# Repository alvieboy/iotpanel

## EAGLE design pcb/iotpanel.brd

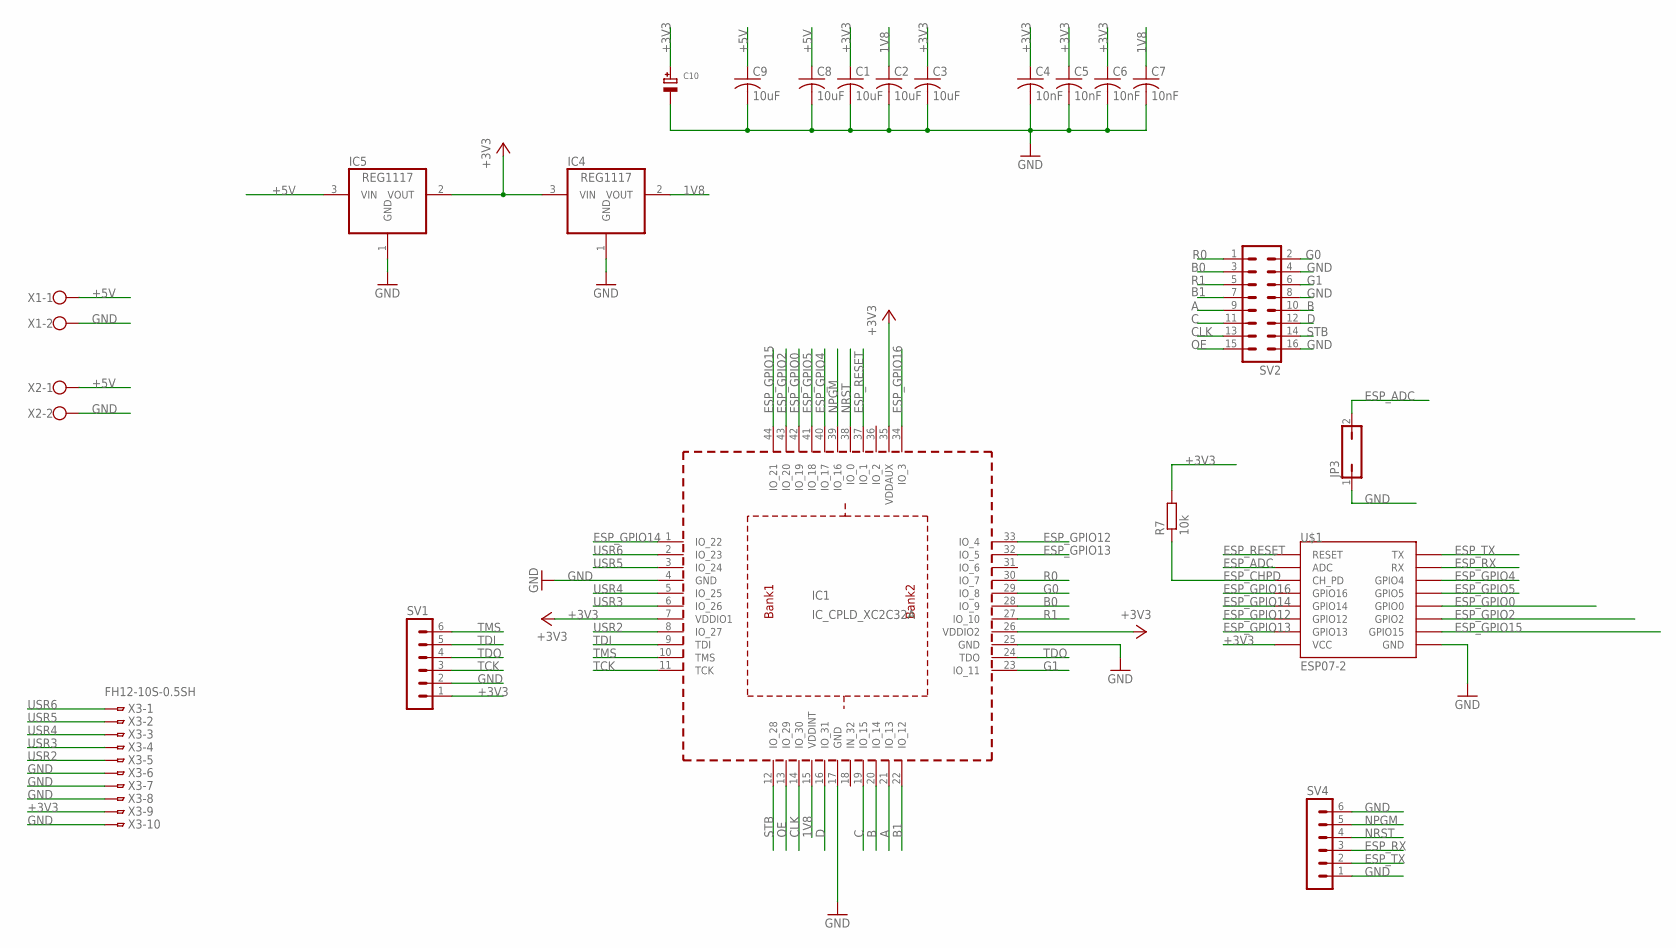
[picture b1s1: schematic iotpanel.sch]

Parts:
C1, C2, C3, C8, C9: 10uF; CAPC0805
C4, C5, C6, C7: 10nF; CAPC0805
C10: CAP_TANTALUMA/3216_WAVE; EIA3216-18/A-W
IC1: IC_CPLD_XC2C32A; VQ-44
IC4, IC5: REG1117; SOT223
JP3: JP1Q; JP1
R7: 10k; R0805
SV1, SV4: MA06-1
SV2: ML16; PARTNO PRPC004DAAN-RC
U$1: ESP07-2
X1, X2: W237-102
X3: FH12-10S-0.5SH

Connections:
1V8: C2.1, C7.1, IC1.15 (VDDINT), IC4.2 (VOUT)
+3V3: C1.1, C3.1, C4.1, C5.1, C6.1, C10.+, IC1.7 (VDDIO1), IC1.26 (VDDIO2), IC1.35 (VDDAUX), IC4.3 (VIN), IC5.2 (VOUT), R7.2, SV1.1, U$1.VCC, X3.9
+5V: C8.1, C9.1, IC5.3 (VIN), X1.1, X2.1
A: IC1.21 (IO_13), SV2.9
B: IC1.20 (IO_14), SV2.10
B0: IC1.28 (IO_9), SV2.3
B1: IC1.22 (IO_12), SV2.7
C: IC1.19 (IO_15), SV2.11
CLK: IC1.14 (IO_30), SV2.13
D: IC1.16 (IO_31), SV2.12
ESP_ADC: JP3.2, U$1.ADC
ESP_CHPD: R7.1, U$1.CH_PD
ESP_GPIO0: IC1.42 (IO_19), U$1.GPIO0
ESP_GPIO2: IC1.43 (IO_20), U$1.GPIO2
ESP_GPIO4: IC1.40 (IO_17), U$1.GPIO4
ESP_GPIO5: IC1.41 (IO_18), U$1.GPIO5
ESP_GPIO12: IC1.33 (IO_4), U$1.GPIO12
ESP_GPIO13: IC1.32 (IO_5), U$1.GPIO13
ESP_GPIO14: IC1.1 (IO_22), U$1.GPIO14
ESP_GPIO15: IC1.44 (IO_21), U$1.GPIO15
ESP_GPIO16: IC1.34 (IO_3), U$1.GPIO16
ESP_RESET: IC1.37 (IO_1), U$1.REST (RESET)
ESP_RX: SV4.3, U$1.RX
ESP_TX: SV4.2, U$1.TX
G0: IC1.29 (IO_8), SV2.2
G1: IC1.23 (IO_11), SV2.6
GND: C1.2, C2.2, C3.2, C4.2, C5.2, C6.2, C7.2, C8.2, C9.2, C10.-, IC1.4 (GND), IC1.17 (GND), IC1.25 (GND), IC4.1 (GND), IC5.1 (GND), JP3.1, SV1.2, SV2.4, SV2.8, SV2.16, SV4.1, SV4.6, U$1.GND, X1.2, X2.2, X3.6, X3.7, X3.8, X3.10
NPGM: IC1.39 (IO_16), SV4.5
NRST: IC1.38 (IO_0), SV4.4
OE: IC1.13 (IO_29), SV2.15
R0: IC1.30 (IO_7), SV2.1
R1: IC1.27 (IO_10), SV2.5
STB: IC1.12 (IO_28), SV2.14
TCK: IC1.11 (TCK), SV1.3
TDI: IC1.9 (TDI), SV1.5
TDO: IC1.24 (TDO), SV1.4
TMS: IC1.10 (TMS), SV1.6
USR2: IC1.8 (IO_27), X3.5
USR3: IC1.6 (IO_26), X3.4
USR4: IC1.5 (IO_25), X3.3
USR5: IC1.3 (IO_24), X3.2
USR6: IC1.2 (IO_23), X3.1

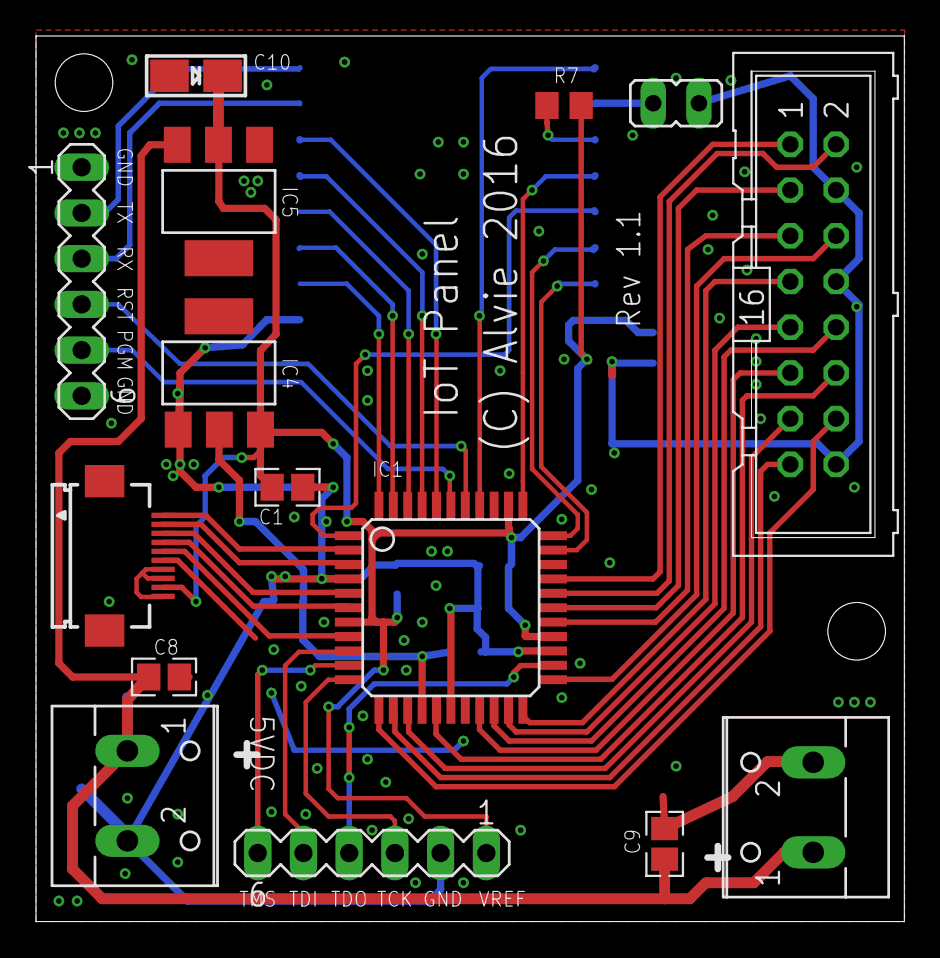
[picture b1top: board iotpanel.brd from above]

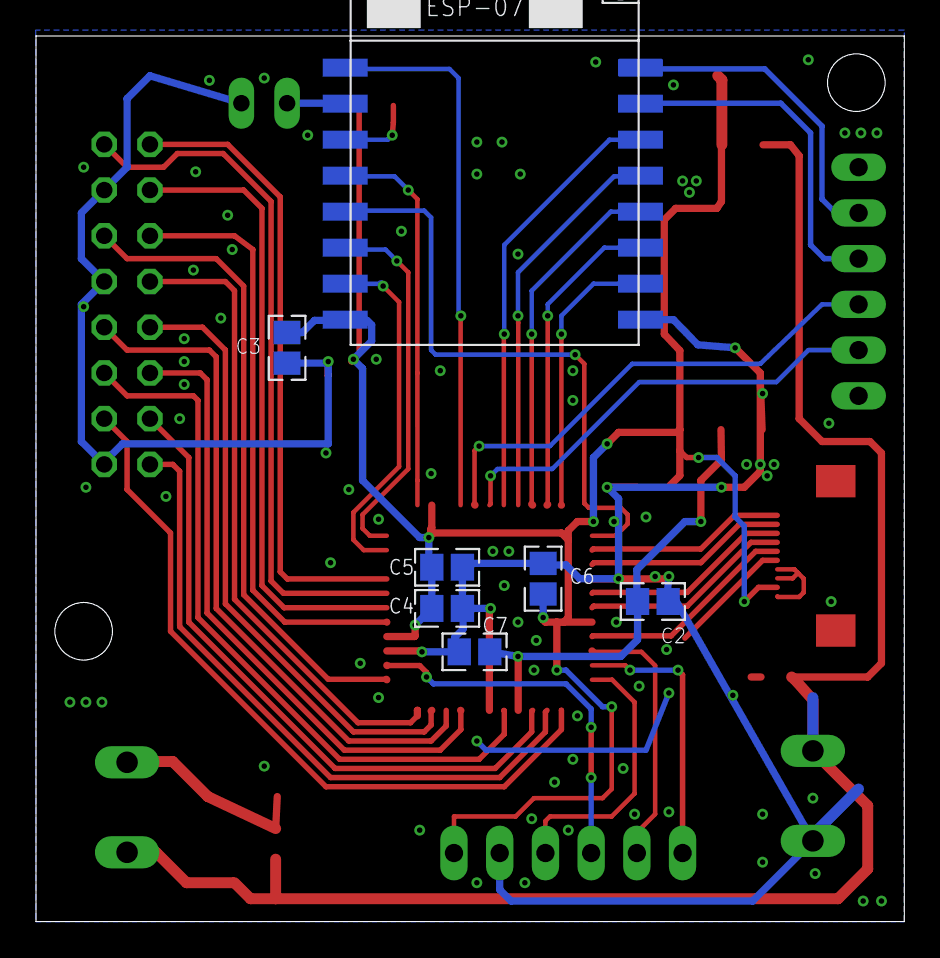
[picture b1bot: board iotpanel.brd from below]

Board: 2 copper layers, 48.2 x 49.2 mm, 22 parts (7 on the bottom side), 42 nets.

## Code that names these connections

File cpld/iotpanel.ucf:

#Created by Constraints Editor (xc2c32a-vq44-4) - 2015/03/27
NET "clk" TNM_NET = clk;
TIMESPEC TS_clk = PERIOD "clk" 12.5 ns HIGH 50%;

NET clk LOC="1" | IOSTANDARD=LVTTL | SLEW=FAST;   # GPIO14
NET cs  LOC="44" | IOSTANDARD=LVTTL | SLEW=FAST | PULLUP; # GPIO15
NET gpio2 LOC="43" | IOSTANDARD=LVTTL | SLEW=FAST | PULLUP;
NET gpio0 LOC="42" | IOSTANDARD=LVTTL | SLEW=FAST ;
NET gpio5 LOC="41" | IOSTANDARD=LVTTL | SLEW=FAST;
NET gpio4 LOC="40" | IOSTANDARD=LVTTL | SLEW=FAST;
NET esprx LOC="39" | IOSTANDARD=LVTTL | SLEW=FAST;
NET esptx LOC="38" | IOSTANDARD=LVTTL | SLEW=FAST;
NET espreset LOC="37" | IOSTANDARD=LVTTL | SLEW=FAST | PULLUP;
#NET espchpd LOC="36" | IOSTANDARD=LVTTL | SLEW=FAST;
NET gpio16 LOC="34" | IOSTANDARD=LVTTL | SLEW=FAST | PULLUP;
NET gpio12 LOC="33" | IOSTANDARD=LVTTL | SLEW=FAST; # DI?
NET gpio13 LOC="32" | IOSTANDARD=LVTTL | SLEW=FAST; # DO?
NET espen LOC="31" | IOSTANDARD=LVTTL | SLEW=FAST;
NET rgb(3) LOC="30" | IOSTANDARD=LVTTL | SLEW=FAST;
NET rgb(4) LOC="29" | IOSTANDARD=LVTTL | SLEW=FAST;
NET rgb(5) LOC="28" | IOSTANDARD=LVTTL | SLEW=FAST;
NET rgb(0) LOC="27" | IOSTANDARD=LVTTL | SLEW=FAST;
NET rgb(1) LOC="23" | IOSTANDARD=LVTTL | SLEW=FAST;
NET rgb(2) LOC="22" | IOSTANDARD=LVTTL | SLEW=FAST;
NET col(0) LOC="21" | IOSTANDARD=LVTTL | SLEW=FAST;
NET col(1) LOC="20" | IOSTANDARD=LVTTL | SLEW=FAST;
NET col(2) LOC="19" | IOSTANDARD=LVTTL | SLEW=FAST;
NET col(3) LOC="12" | IOSTANDARD=LVTTL | SLEW=FAST;
NET iusr LOC="18" | IOSTANDARD=LVTTL | SLEW=FAST;
NET clko LOC="16" | IOSTANDARD=LVTTL | SLEW=FAST;
NET oe LOC="14" | IOSTANDARD=LVTTL | SLEW=FAST;
NET stb LOC="13" | IOSTANDARD=LVTTL | SLEW=FAST;
NET panelen LOC="8" | IOSTANDARD=LVTTL | SLEW=FAST;
NET usr(3) LOC="6" | IOSTANDARD=LVTTL | SLEW=FAST;
NET usr(4) LOC="5" | IOSTANDARD=LVTTL | SLEW=FAST;
NET usr(5) LOC="3" | IOSTANDARD=LVTTL | SLEW=FAST;
NET usr(6) LOC="2" | IOSTANDARD=LVTTL | SLEW=FAST;

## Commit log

2015-05-25 Add PCB and CPLD design
2015-05-25 Add firmware
2015-05-25 Add esptool (modified)
2015-05-25 Add prebuilt CPLD JED file
2015-06-09 sync CPLD (new version) and base code
2015-06-14 Synchronize
2015-06-14 Fix widget name, add destroy
2015-06-14 prototype work
2015-06-14 Add WIPE commadn
2015-06-14 Fix propset name
2015-06-23 Widget improvements, code reorganization
2015-06-23 Linux panel version (for testing)
2015-06-23 Add preliminary clock
2015-06-23 Fix brightness on last line of each panel
2015-06-23 Widget fixes, better linux display
2015-06-24 Enforce no-reset. May help with spurious resets
2015-06-24 Add networking
2015-06-24 Add new text widget, clean up some code
2015-06-24 Add text widget
2015-06-24 fix return value
2015-06-25 Several fixes
2015-06-29 Add calloc
2015-06-29 Bunch of changes/fixes
2015-06-30 Cleanups and system_get_time() impl. Preparation for win32
2015-06-30 Batch update
2015-08-19 disable debug, don't start schedule if disabled
2015-08-20 Add missing clock widget
2015-08-21 Fix clone argument size
2015-10-07 Add iotlogin
2015-10-31 Pool app
2015-11-06 Improvements
2015-11-23 OTA upgrades and new files
2015-11-27 Several updates
2015-12-01 Snapshot
2015-12-05 missing
2016-01-01 Fix blanking and start with lower power consumption
2016-01-01 Enable debug under Linux
2016-01-01 Don't store fonts in ICACHE
2016-01-01 Add text wrapping
2016-01-01 Fix connection close and connection argument
2016-01-01 reorganize flash stuff
2016-01-01 Disable AP mode: not working
2016-01-01 update default design and propagate MAC on broadcasts
2016-01-01 new serialization code
2016-01-01 Add flash serializer
2016-01-01 add crc engine
2016-01-01 New serialization
2016-01-01 Proper getter implementation for serialization
2016-01-03 Fixups in linux version
2016-01-03 Cleanups, and remove unnecessary comparison
2016-01-03 CRC cleanups
2016-01-03 Finish CRC checks
2016-01-03 Some schedule cleanups and serialization stuff
2016-01-03 Add SAVE command
2016-01-03 Use flash design if present
2016-01-03 Finish serialization
2016-01-09 Fixes all around...
2016-01-17 OTA stable
2016-01-17 Use gray code for row selection, improve timings to avoid interference
2016-01-17 Disable soft watchdog, add watchdog kick
2016-01-23 Allow linux version to build cleanly
2016-01-23 Dont use NMI, fix build in linux
2016-01-23 rgb332 first implementation
2016-01-24 RGB332
2016-02-04 attempt
2016-02-04 Fix testbench pin assignments
2016-02-05 Working version at 97Hz
2016-02-07 timing improvements and tests
2016-02-07 Add v1.1 board
2016-02-09 Several fixes all around
2016-02-09 QT version
2016-02-10 Add layout
2016-02-10 Some commits seem to be missing
2016-02-12 Add smallfs
2016-02-12 New flash infrasctructure
2016-02-12 Memory improvements
2016-02-12 Fix linux build
2016-02-12 New font infrastructure
2016-02-12 Add new QT version
2016-04-06 Fix serialization and add some debugging
2016-04-06 Fix text rendering
2016-04-06 Remove debugging on serialization
2016-04-06 Fix cloned widgets and socket closing
2016-04-06 Fix scrolling text rendering
2016-04-06 Connect to best RSSI AP
2016-04-06 Use proper smallfs
2016-04-06 Add rom image
2016-04-06 Add rom images
2016-04-06 Remove useless code
2016-04-07 Add realloc
2016-04-07 Add GIF support
2016-04-07 Add ROM image support
2016-04-09 Allow FPS reporting, add 64-bit transfer (preliminar)
2016-04-09 Add error routines and defines
2016-04-09 Better error handling
2016-04-17 JSW test
2016-04-17 Add JSW
2016-04-17 Add preliminary webserver/websocket
2016-04-17 Fix includes
2016-04-28 Add SSL, use Os
2016-04-28 Batch of updates
2016-05-01 Add new error code
2016-05-01 Fix/implement auth
2016-05-01 Implement login
2016-05-01 Move SHA stuff
2016-05-03 Optional preloading
2016-05-03 Warn
2016-05-03 debug optimizations
2016-05-04 Add file headers
2016-05-04 Add rom
2016-05-04 Fix comparisons
2016-11-27 Fix cleanup of romimage
2016-11-27 update project
2017-01-17 Fix blanking
2017-01-21 Sync
2017-01-21 disable WS
2017-01-21 disable GIF
2017-01-21 Text rotate and flip
2017-01-21 allow H to be reversed
2017-01-21 Add OTA flag
2017-01-21 Enable c++11
2017-01-21 Remove autogen file
2017-01-21 Game updates
2017-01-21 Slow down a bit
2017-01-21 Use new piece layout to match original game rotation
2017-01-21 Split pieces, remove debug
2017-01-21 New color infrastructure
2017-01-21 Clean up code a bit

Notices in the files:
parts and their libraries:
microbuilder: This work is placed in the public domain, and may be freely used for commercial and non-commercial work with the following conditions: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
